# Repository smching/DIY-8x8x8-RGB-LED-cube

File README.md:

# DIY 8x8x8 RGB LED cube

Thank you my friend Siew Goh Chuang, he made this beautiful LED cube:  This is a 8x8x8 RGB LED cube project, a modified version of the LED cube which originally designed by Kavindarrah:

http://www.kevindarrah.com

This project only modified the hardware but leaving the software (source code) intact. All the source code is available in Kavindarrah's website.

Documentation is available at  http://ediy.com.my/index.php/projects/item/135-diy-8x8x8-rgb-led-cube

Flickr album: https://www.flickr.com/photos/ediy2u/albums/72157663117824245

Youtube video: https://youtu.be/O3SzMkJ8tPI

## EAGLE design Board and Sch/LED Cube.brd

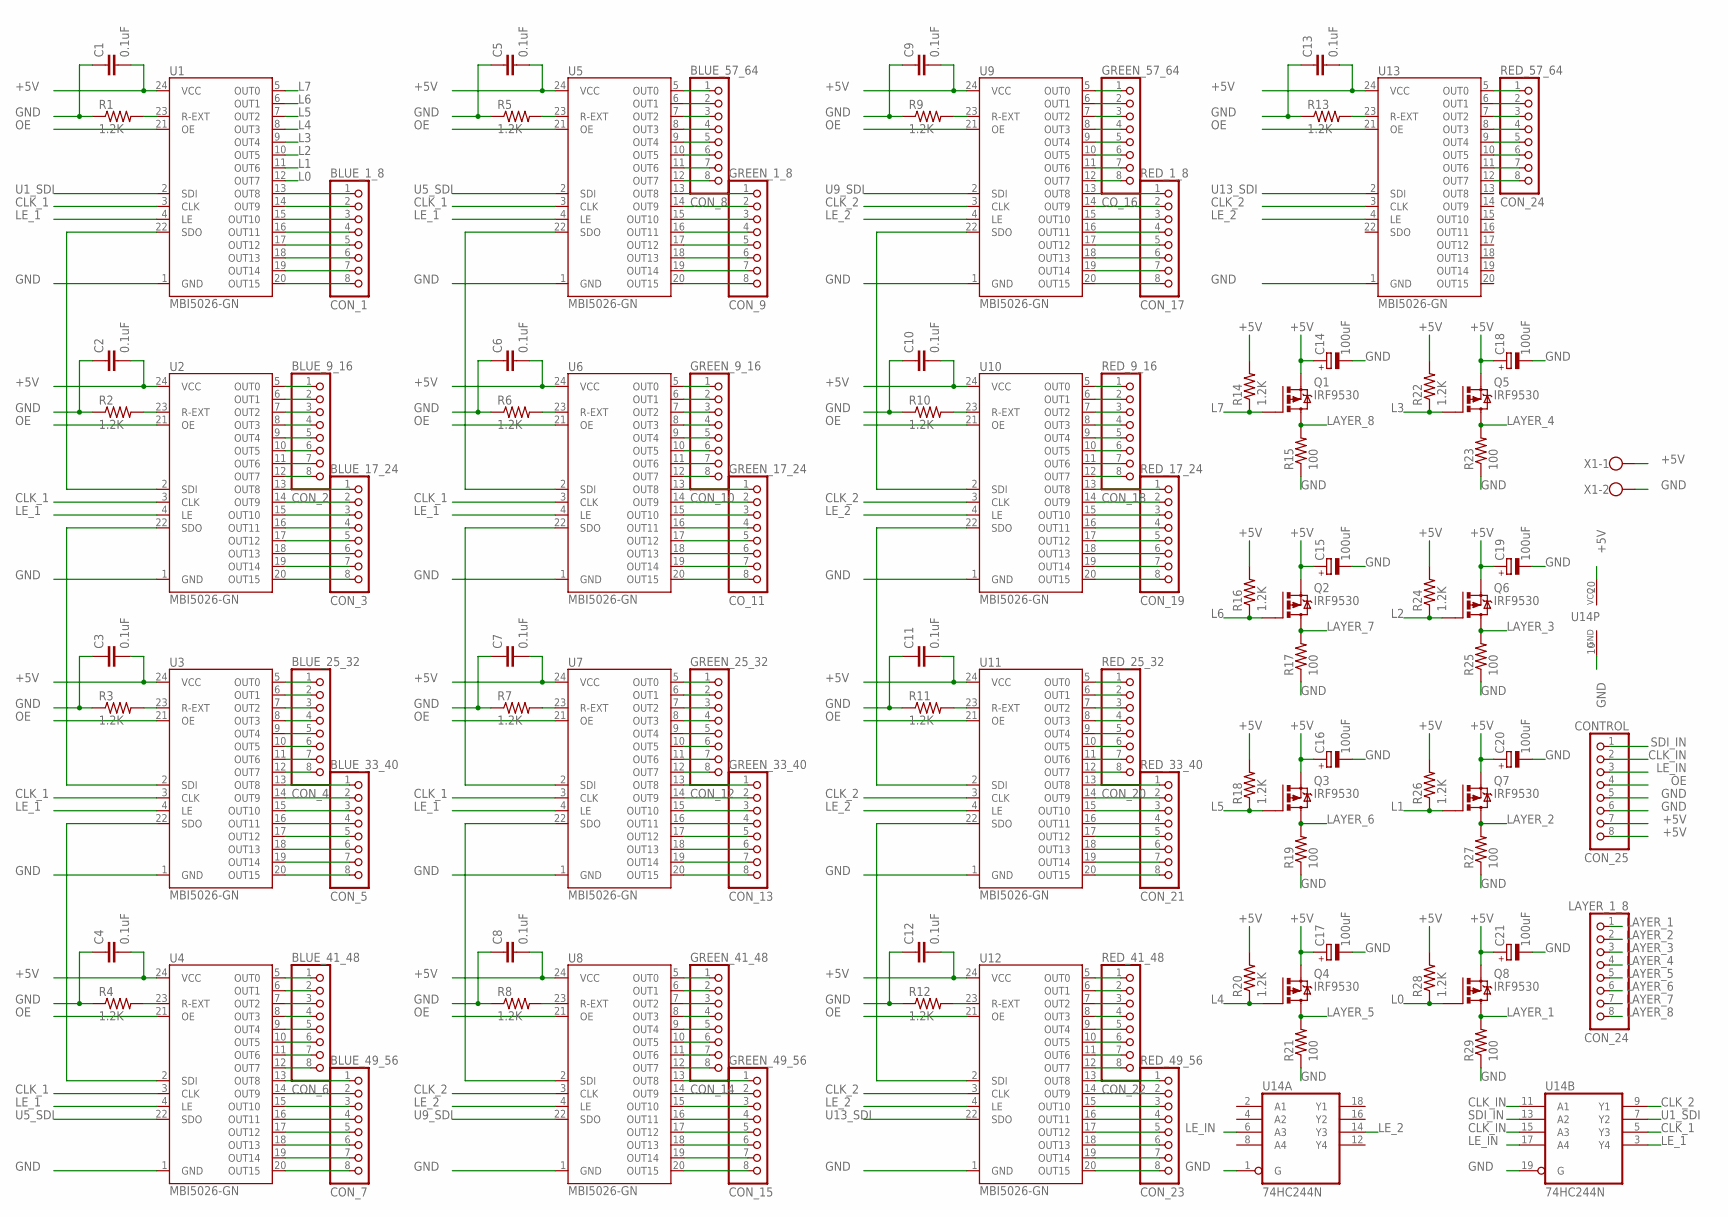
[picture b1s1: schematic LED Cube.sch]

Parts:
BLUE_1_8: CON_1; 1X08-BIG
BLUE_9_16: CON_2; 1X08-BIG
BLUE_17_24: CON_3; 1X08-BIG
BLUE_25_32: CON_4; 1X08-BIG
BLUE_33_40: CON_5; 1X08-BIG
BLUE_41_48: CON_6; 1X08-BIG
BLUE_49_56: CON_7; 1X08-BIG
BLUE_57_64: CON_8; 1X08-BIG
C1, C2, C3, C4, C5, C6, C7, C8, C9, C10, C11, C12, C13: 0.1uF; C2.5-3
C14, C15, C16, C17, C18, C19, C20, C21: 100uF; E5-6
CONTROL: CON_25; 1X08-BIG
GREEN_1_8: CON_9; 1X08-BIG
GREEN_9_16: CON_10; 1X08-BIG
GREEN_17_24: CO_11; 1X08-BIG
GREEN_25_32: CON_12; 1X08-BIG
GREEN_33_40: CON_13; 1X08-BIG
GREEN_41_48: CON_14; 1X08-BIG
GREEN_49_56: CON_15; 1X08-BIG
GREEN_57_64: CO_16; 1X08-BIG
LAYER_1_8: CON_24; 1X08-BIG
Q1, Q2, Q3, Q4, Q5, Q6, Q7, Q8: IRF9530; TO220BV
R1, R2, R3, R4, R5, R6, R7, R8, R9, R10, R11, R12, R13, R14, R16, R18, R20, R22, R24, R26, R28: 1.2K; 0207/15
R15, R17, R19, R21, R23, R25, R27, R29: 100; 0207/15
RED_1_8: CON_17; 1X08-BIG
RED_9_16: CON_18; 1X08-BIG
RED_17_24: CON_19; 1X08-BIG
RED_25_32: CON_20; 1X08-BIG
RED_33_40: CON_21; 1X08-BIG
RED_41_48: CON_22; 1X08-BIG
RED_49_56: CON_23; 1X08-BIG
RED_57_64: CON_24; 1X08-BIG
U1, U2, U3, U4, U5, U6, U7, U8, U9, U10, U11, U12, U13: MBI5026-GN; DIL24-3
U14: 74HC244N; DIL20
X1: W237-102

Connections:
+5V: C1.2, C2.2, C3.2, C4.2, C5.2, C6.2, C7.2, C8.2, C9.2, C10.2, C11.2, C12.2, C13.2, C14.+, C15.+, C16.+, C17.+, C18.+, C19.+, C20.+, C21.+, CONTROL.7, CONTROL.8, Q1.S, Q2.S, Q3.S, Q4.S, Q5.S, Q6.S, Q7.S, Q8.S, R14.2, R16.2, R18.2, R20.2, R22.2, R24.2, R26.2, R28.2, U1.24 (VCC), U2.24 (VCC), U3.24 (VCC), U4.24 (VCC), U5.24 (VCC), U6.24 (VCC), U7.24 (VCC), U8.24 (VCC), U9.24 (VCC), U10.24 (VCC), U11.24 (VCC), U12.24 (VCC), U13.24 (VCC), U14.20 (VCC), X1.1
CLK_1: U1.3 (CLK), U2.3 (CLK), U3.3 (CLK), U4.3 (CLK), U5.3 (CLK), U6.3 (CLK), U7.3 (CLK), U14.5 (Y3)
CLK_2: U8.3 (CLK), U9.3 (CLK), U10.3 (CLK), U11.3 (CLK), U12.3 (CLK), U13.3 (CLK), U14.9 (Y1)
CLK_IN: CONTROL.2, U14.11 (A1), U14.15 (A3)
GND: C1.1, C2.1, C3.1, C4.1, C5.1, C6.1, C7.1, C8.1, C9.1, C10.1, C11.1, C12.1, C13.1, C14.-, C15.-, C16.-, C17.-, C18.-, C19.-, C20.-, C21.-, CONTROL.5, CONTROL.6, R1.1, R2.1, R3.1, R4.1, R5.1, R6.1, R7.1, R8.1, R9.1, R10.1, R11.1, R12.1, R13.1, R15.1, R17.1, R19.1, R21.1, R23.1, R25.1, R27.1, R29.1, U1.1 (GND), U2.1 (GND), U3.1 (GND), U4.1 (GND), U5.1 (GND), U6.1 (GND), U7.1 (GND), U8.1 (GND), U9.1 (GND), U10.1 (GND), U11.1 (GND), U12.1 (GND), U13.1 (GND), U14.1 (G), U14.10 (GND), U14.19 (G), X1.2
L0: Q8.G, R28.1, U1.12 (OUT7)
L1: Q7.G, R26.1, U1.11 (OUT6)
L2: Q6.G, R24.1, U1.10 (OUT5)
L3: Q5.G, R22.1, U1.9 (OUT4)
L4: Q4.G, R20.1, U1.8 (OUT3)
L5: Q3.G, R18.1, U1.7 (OUT2)
L6: Q2.G, R16.1, U1.6 (OUT1)
L7: Q1.G, R14.1, U1.5 (OUT0)
LAYER_1: LAYER_1_8.1, Q8.D, R29.2
LAYER_2: LAYER_1_8.2, Q7.D, R27.2
LAYER_3: LAYER_1_8.3, Q6.D, R25.2
LAYER_4: LAYER_1_8.4, Q5.D, R23.2
LAYER_5: LAYER_1_8.5, Q4.D, R21.2
LAYER_6: LAYER_1_8.6, Q3.D, R19.2
LAYER_7: LAYER_1_8.7, Q2.D, R17.2
LAYER_8: LAYER_1_8.8, Q1.D, R15.2
LE_1: U1.4 (LE), U2.4 (LE), U3.4 (LE), U4.4 (LE), U5.4 (LE), U6.4 (LE), U7.4 (LE), U14.3 (Y4)
LE_2: U8.4 (LE), U9.4 (LE), U10.4 (LE), U11.4 (LE), U12.4 (LE), U13.4 (LE), U14.14 (Y3)
LE_IN: CONTROL.3, U14.6 (A3), U14.17 (A4)
unnamed: U1.22 (SDO), U2.2 (SDI)
unnamed: BLUE_1_8.1, U1.13 (OUT8)
unnamed: BLUE_1_8.2, U1.14 (OUT9)
unnamed: BLUE_1_8.3, U1.15 (OUT10)
unnamed: R2.2, U2.23 (R-EXT)
unnamed: U2.22 (SDO), U3.2 (SDI)
unnamed: BLUE_1_8.4, U1.16 (OUT11)
unnamed: BLUE_1_8.5, U1.17 (OUT12)
unnamed: BLUE_1_8.6, U1.18 (OUT13)
unnamed: R3.2, U3.23 (R-EXT)
unnamed: U3.22 (SDO), U4.2 (SDI)
unnamed: BLUE_1_8.7, U1.19 (OUT14)
unnamed: BLUE_1_8.8, U1.20 (OUT15)
unnamed: R4.2, U4.23 (R-EXT)
unnamed: BLUE_9_16.1, U2.5 (OUT0)
unnamed: BLUE_9_16.2, U2.6 (OUT1)
unnamed: BLUE_9_16.3, U2.7 (OUT2)
unnamed: R1.2, U1.23 (R-EXT)
unnamed: BLUE_9_16.4, U2.8 (OUT3)
unnamed: BLUE_9_16.5, U2.9 (OUT4)
unnamed: R5.2, U5.23 (R-EXT)
unnamed: U5.22 (SDO), U6.2 (SDI)
unnamed: BLUE_9_16.6, U2.10 (OUT5)
unnamed: BLUE_9_16.7, U2.11 (OUT6)
unnamed: R6.2, U6.23 (R-EXT)
unnamed: U6.22 (SDO), U7.2 (SDI)
unnamed: BLUE_9_16.8, U2.12 (OUT7)
unnamed: BLUE_17_24.1, U2.13 (OUT8)
unnamed: BLUE_17_24.2, U2.14 (OUT9)
unnamed: BLUE_17_24.3, U2.15 (OUT10)
unnamed: R7.2, U7.23 (R-EXT)
unnamed: U7.22 (SDO), U8.2 (SDI)
unnamed: BLUE_17_24.4, U2.16 (OUT11)
unnamed: BLUE_17_24.5, U2.17 (OUT12)
unnamed: R8.2, U8.23 (R-EXT)
unnamed: BLUE_17_24.6, U2.18 (OUT13)
unnamed: BLUE_17_24.7, U2.19 (OUT14)
unnamed: BLUE_17_24.8, U2.20 (OUT15)
unnamed: BLUE_25_32.1, U3.5 (OUT0)
unnamed: BLUE_25_32.2, U3.6 (OUT1)
unnamed: R9.2, U9.23 (R-EXT)
unnamed: U9.22 (SDO), U10.2 (SDI)
unnamed: BLUE_25_32.3, U3.7 (OUT2)
unnamed: BLUE_25_32.4, U3.8 (OUT3)
unnamed: R10.2, U10.23 (R-EXT)
unnamed: U10.22 (SDO), U11.2 (SDI)
unnamed: BLUE_25_32.5, U3.9 (OUT4)
unnamed: BLUE_25_32.6, U3.10 (OUT5)
unnamed: BLUE_25_32.7, U3.11 (OUT6)
unnamed: BLUE_25_32.8, U3.12 (OUT7)
unnamed: R11.2, U11.23 (R-EXT)
unnamed: U11.22 (SDO), U12.2 (SDI)
unnamed: BLUE_33_40.1, U3.13 (OUT8)
unnamed: BLUE_33_40.2, U3.14 (OUT9)
unnamed: R12.2, U12.23 (R-EXT)
unnamed: BLUE_33_40.3, U3.15 (OUT10)
unnamed: BLUE_33_40.4, U3.16 (OUT11)
unnamed: BLUE_33_40.5, U3.17 (OUT12)
unnamed: BLUE_33_40.6, U3.18 (OUT13)
unnamed: BLUE_33_40.7, U3.19 (OUT14)
unnamed: BLUE_33_40.8, U3.20 (OUT15)
unnamed: R13.2, U13.23 (R-EXT)
unnamed: BLUE_41_48.1, U4.5 (OUT0)
unnamed: BLUE_41_48.2, U4.6 (OUT1)
unnamed: BLUE_41_48.3, U4.7 (OUT2)
unnamed: BLUE_41_48.4, U4.8 (OUT3)
unnamed: BLUE_41_48.5, U4.9 (OUT4)
unnamed: BLUE_41_48.6, U4.10 (OUT5)
unnamed: BLUE_41_48.7, U4.11 (OUT6)
unnamed: BLUE_41_48.8, U4.12 (OUT7)
unnamed: BLUE_49_56.1, U4.13 (OUT8)
unnamed: BLUE_49_56.2, U4.14 (OUT9)
unnamed: BLUE_49_56.3, U4.15 (OUT10)
unnamed: BLUE_49_56.4, U4.16 (OUT11)
unnamed: BLUE_49_56.5, U4.17 (OUT12)
unnamed: BLUE_49_56.6, U4.18 (OUT13)
unnamed: BLUE_49_56.7, U4.19 (OUT14)
unnamed: BLUE_49_56.8, U4.20 (OUT15)
unnamed: BLUE_57_64.1, U5.5 (OUT0)
unnamed: BLUE_57_64.2, U5.6 (OUT1)
unnamed: BLUE_57_64.3, U5.7 (OUT2)
unnamed: BLUE_57_64.4, U5.8 (OUT3)
unnamed: BLUE_57_64.5, U5.9 (OUT4)
unnamed: BLUE_57_64.6, U5.10 (OUT5)
unnamed: BLUE_57_64.7, U5.11 (OUT6)
unnamed: BLUE_57_64.8, U5.12 (OUT7)
unnamed: GREEN_1_8.1, U5.13 (OUT8)
unnamed: GREEN_1_8.2, U5.14 (OUT9)
unnamed: GREEN_1_8.3, U5.15 (OUT10)
unnamed: GREEN_1_8.4, U5.16 (OUT11)
unnamed: GREEN_1_8.5, U5.17 (OUT12)
unnamed: GREEN_1_8.6, U5.18 (OUT13)
unnamed: GREEN_1_8.7, U5.19 (OUT14)
unnamed: GREEN_1_8.8, U5.20 (OUT15)
unnamed: GREEN_9_16.1, U6.5 (OUT0)
unnamed: GREEN_9_16.2, U6.6 (OUT1)
unnamed: GREEN_9_16.3, U6.7 (OUT2)
unnamed: GREEN_9_16.4, U6.8 (OUT3)
unnamed: GREEN_9_16.5, U6.9 (OUT4)
unnamed: GREEN_9_16.6, U6.10 (OUT5)
unnamed: GREEN_9_16.7, U6.11 (OUT6)
unnamed: GREEN_9_16.8, U6.12 (OUT7)
unnamed: GREEN_17_24.1, U6.13 (OUT8)
unnamed: GREEN_17_24.2, U6.14 (OUT9)
unnamed: GREEN_17_24.3, U6.15 (OUT10)
unnamed: GREEN_17_24.4, U6.16 (OUT11)
unnamed: GREEN_17_24.5, U6.17 (OUT12)
unnamed: GREEN_17_24.6, U6.18 (OUT13)
unnamed: GREEN_17_24.7, U6.19 (OUT14)
unnamed: GREEN_17_24.8, U6.20 (OUT15)
unnamed: GREEN_25_32.1, U7.5 (OUT0)
unnamed: GREEN_25_32.2, U7.6 (OUT1)
unnamed: GREEN_25_32.3, U7.7 (OUT2)
unnamed: GREEN_25_32.4, U7.8 (OUT3)
unnamed: GREEN_25_32.5, U7.9 (OUT4)
unnamed: GREEN_25_32.6, U7.10 (OUT5)
unnamed: GREEN_25_32.7, U7.11 (OUT6)
unnamed: GREEN_25_32.8, U7.12 (OUT7)
unnamed: GREEN_33_40.1, U7.13 (OUT8)
unnamed: GREEN_33_40.2, U7.14 (OUT9)
unnamed: GREEN_33_40.3, U7.15 (OUT10)
unnamed: GREEN_33_40.4, U7.16 (OUT11)
unnamed: GREEN_33_40.5, U7.17 (OUT12)
unnamed: GREEN_33_40.6, U7.18 (OUT13)
unnamed: GREEN_33_40.7, U7.19 (OUT14)
unnamed: GREEN_33_40.8, U7.20 (OUT15)
unnamed: GREEN_41_48.1, U8.5 (OUT0)
unnamed: GREEN_41_48.2, U8.6 (OUT1)
unnamed: GREEN_41_48.3, U8.7 (OUT2)
unnamed: GREEN_41_48.4, U8.8 (OUT3)
unnamed: GREEN_41_48.5, U8.9 (OUT4)
unnamed: GREEN_41_48.6, U8.10 (OUT5)
unnamed: GREEN_41_48.7, U8.11 (OUT6)
unnamed: GREEN_41_48.8, U8.12 (OUT7)
unnamed: GREEN_49_56.1, U8.13 (OUT8)
unnamed: GREEN_49_56.2, U8.14 (OUT9)
unnamed: GREEN_49_56.3, U8.15 (OUT10)
unnamed: GREEN_49_56.4, U8.16 (OUT11)
unnamed: GREEN_49_56.5, U8.17 (OUT12)
unnamed: GREEN_49_56.6, U8.18 (OUT13)
unnamed: GREEN_49_56.7, U8.19 (OUT14)
unnamed: GREEN_49_56.8, U8.20 (OUT15)
unnamed: GREEN_57_64.1, U9.5 (OUT0)
unnamed: GREEN_57_64.2, U9.6 (OUT1)
unnamed: GREEN_57_64.3, U9.7 (OUT2)
unnamed: GREEN_57_64.4, U9.8 (OUT3)
unnamed: GREEN_57_64.5, U9.9 (OUT4)
unnamed: GREEN_57_64.6, U9.10 (OUT5)
unnamed: GREEN_57_64.7, U9.11 (OUT6)
unnamed: GREEN_57_64.8, U9.12 (OUT7)
unnamed: RED_1_8.1, U9.13 (OUT8)
unnamed: RED_1_8.2, U9.14 (OUT9)
unnamed: RED_1_8.3, U9.15 (OUT10)
unnamed: RED_1_8.4, U9.16 (OUT11)
unnamed: RED_1_8.5, U9.17 (OUT12)
unnamed: RED_1_8.6, U9.18 (OUT13)
unnamed: RED_1_8.7, U9.19 (OUT14)
unnamed: RED_1_8.8, U9.20 (OUT15)
unnamed: RED_9_16.1, U10.5 (OUT0)
unnamed: RED_9_16.2, U10.6 (OUT1)
unnamed: RED_9_16.3, U10.7 (OUT2)
unnamed: RED_9_16.4, U10.8 (OUT3)
unnamed: RED_9_16.5, U10.9 (OUT4)
unnamed: RED_9_16.6, U10.10 (OUT5)
unnamed: RED_9_16.7, U10.11 (OUT6)
unnamed: RED_9_16.8, U10.12 (OUT7)
unnamed: RED_17_24.1, U10.13 (OUT8)
unnamed: RED_17_24.2, U10.14 (OUT9)
unnamed: RED_17_24.3, U10.15 (OUT10)
unnamed: RED_17_24.4, U10.16 (OUT11)
unnamed: RED_17_24.5, U10.17 (OUT12)
unnamed: RED_17_24.6, U10.18 (OUT13)
unnamed: RED_17_24.7, U10.19 (OUT14)
unnamed: RED_17_24.8, U10.20 (OUT15)
unnamed: RED_25_32.1, U11.5 (OUT0)
unnamed: RED_25_32.2, U11.6 (OUT1)
unnamed: RED_25_32.3, U11.7 (OUT2)
unnamed: RED_25_32.4, U11.8 (OUT3)
unnamed: RED_25_32.5, U11.9 (OUT4)
unnamed: RED_25_32.6, U11.10 (OUT5)
unnamed: RED_25_32.7, U11.11 (OUT6)
unnamed: RED_25_32.8, U11.12 (OUT7)
unnamed: RED_33_40.1, U11.13 (OUT8)
unnamed: RED_33_40.2, U11.14 (OUT9)
unnamed: RED_33_40.3, U11.15 (OUT10)
unnamed: RED_33_40.4, U11.16 (OUT11)
unnamed: RED_33_40.5, U11.17 (OUT12)
unnamed: RED_33_40.6, U11.18 (OUT13)
unnamed: RED_33_40.7, U11.19 (OUT14)
unnamed: RED_33_40.8, U11.20 (OUT15)
unnamed: RED_41_48.1, U12.5 (OUT0)
unnamed: RED_41_48.2, U12.6 (OUT1)
unnamed: RED_41_48.3, U12.7 (OUT2)
unnamed: RED_41_48.4, U12.8 (OUT3)
unnamed: RED_41_48.5, U12.9 (OUT4)
unnamed: RED_41_48.6, U12.10 (OUT5)
unnamed: RED_41_48.7, U12.11 (OUT6)
unnamed: RED_41_48.8, U12.12 (OUT7)
unnamed: RED_49_56.1, U12.13 (OUT8)
unnamed: RED_49_56.2, U12.14 (OUT9)
unnamed: RED_49_56.3, U12.15 (OUT10)
unnamed: RED_49_56.4, U12.16 (OUT11)
unnamed: RED_49_56.5, U12.17 (OUT12)
unnamed: RED_49_56.6, U12.18 (OUT13)
unnamed: RED_49_56.7, U12.19 (OUT14)
unnamed: RED_49_56.8, U12.20 (OUT15)
unnamed: RED_57_64.1, U13.5 (OUT0)
unnamed: RED_57_64.2, U13.6 (OUT1)
unnamed: RED_57_64.3, U13.7 (OUT2)
unnamed: RED_57_64.4, U13.8 (OUT3)
unnamed: RED_57_64.5, U13.9 (OUT4)
unnamed: RED_57_64.6, U13.10 (OUT5)
unnamed: RED_57_64.7, U13.11 (OUT6)
unnamed: RED_57_64.8, U13.12 (OUT7)
OE: CONTROL.4, U1.21 (OE), U2.21 (OE), U3.21 (OE), U4.21 (OE), U5.21 (OE), U6.21 (OE), U7.21 (OE), U8.21 (OE), U9.21 (OE), U10.21 (OE), U11.21 (OE), U12.21 (OE), U13.21 (OE)
SDI_IN: CONTROL.1, U14.13 (A2)
U1_SDI: U1.2 (SDI), U14.7 (Y2)
U5_SDI: U4.22 (SDO), U5.2 (SDI)
U9_SDI: U8.22 (SDO), U9.2 (SDI)
U13_SDI: U12.22 (SDO), U13.2 (SDI)

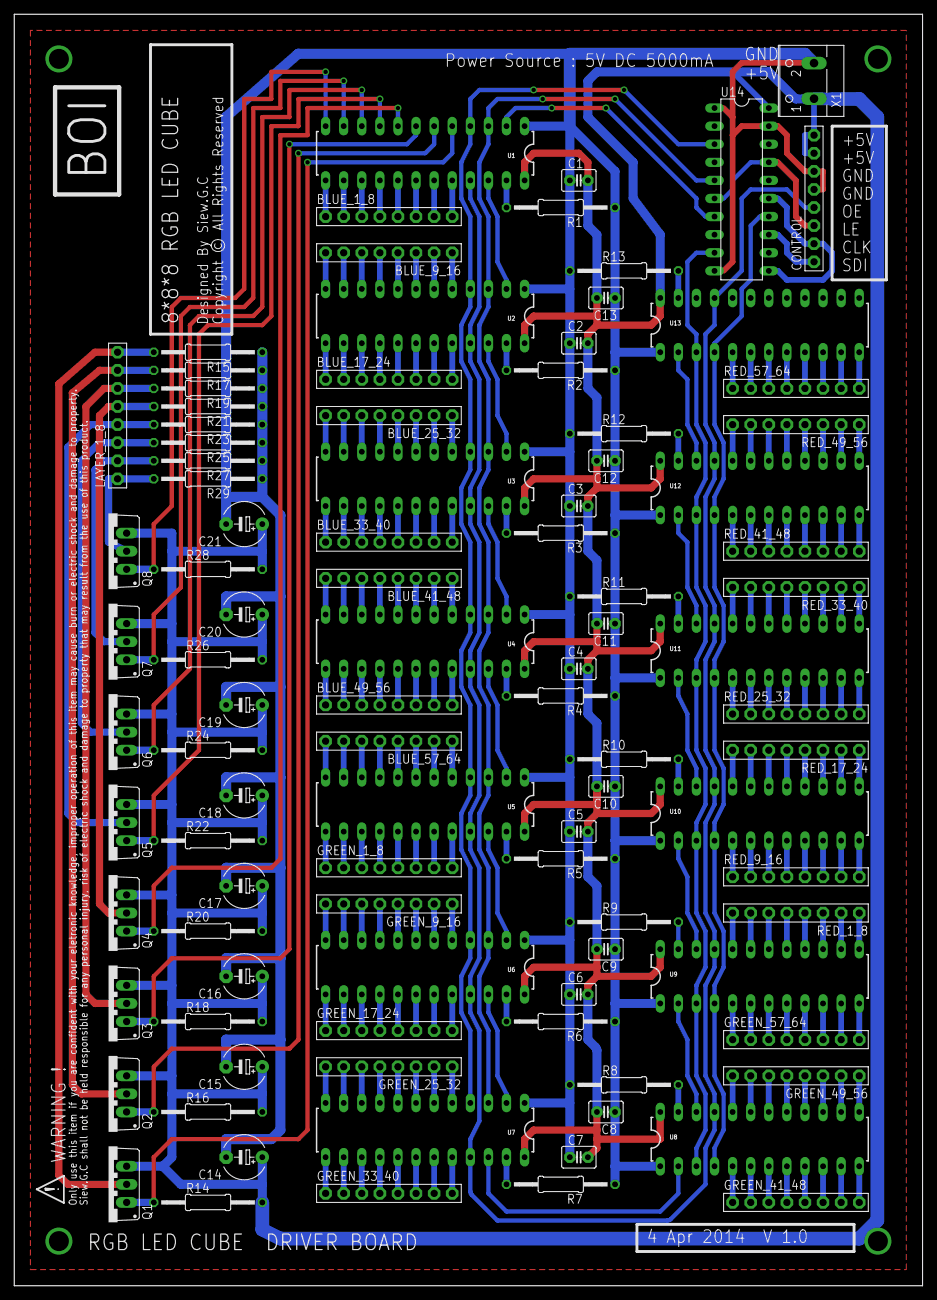
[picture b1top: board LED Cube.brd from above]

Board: 2 copper layers, 127.5 x 178.5 mm, 99 parts (0 on the bottom side), 244 nets.

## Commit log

2016-01-04 :space_invader: Added .gitattributes & .gitignore files
2016-01-04 Rev 11
2016-01-04 Rev 12
2016-01-04 Rev 7

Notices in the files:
Board and Sch/LED Cube.brd:
Copyright © All Rights Reserved
